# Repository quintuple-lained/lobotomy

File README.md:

# Lobotomy
*The keyboard your therapist told you to worry about.*

An unholy mixture of Alice and Bruce, have fun with this one y'all!

## Images

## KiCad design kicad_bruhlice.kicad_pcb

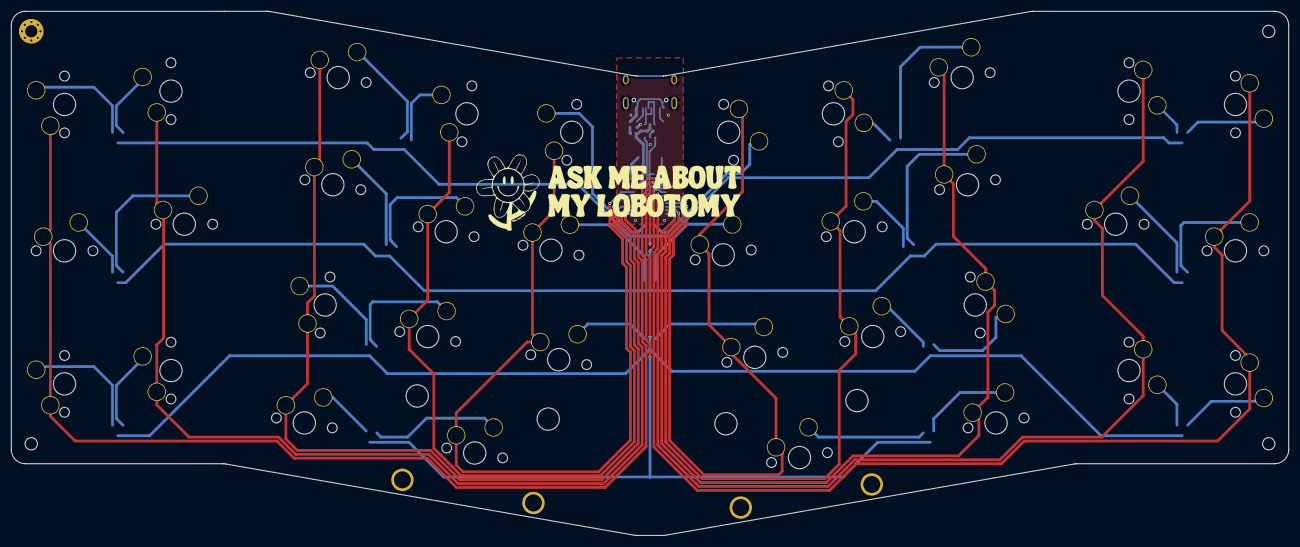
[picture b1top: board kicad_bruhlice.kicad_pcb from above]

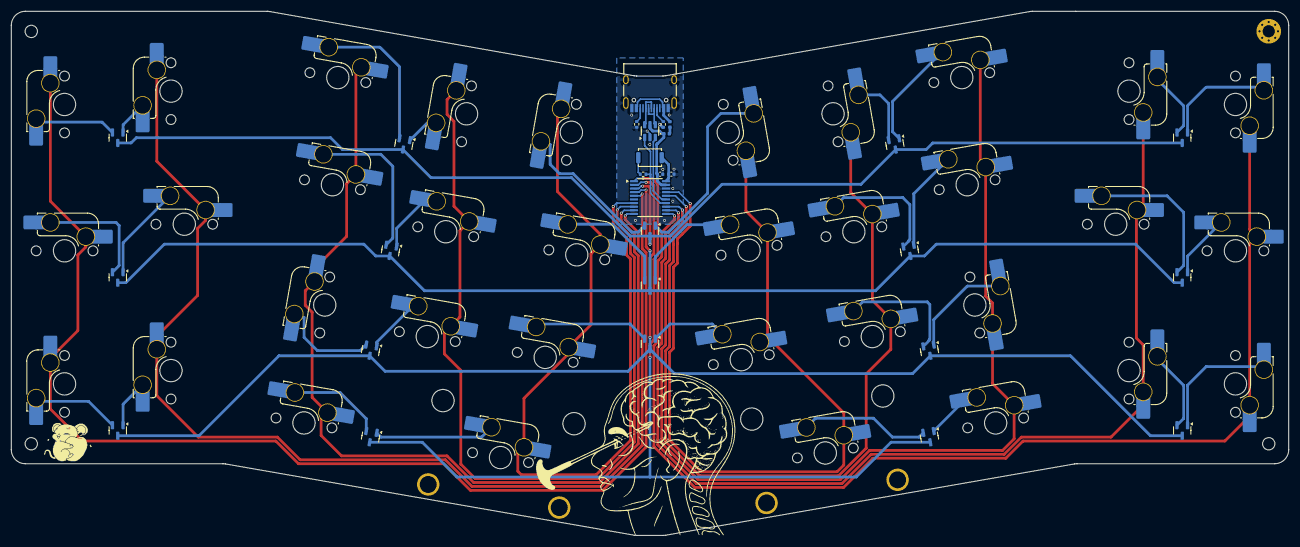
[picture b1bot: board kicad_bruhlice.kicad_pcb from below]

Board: 2 copper layers, 228.6 x 93.8 mm, 68 parts (62 on the bottom side), 60 nets.

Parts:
C1, C2: 100nF; C_0402_1005Metric
D1: PMEG2010EA; D_0402_1005Metric
D2, D3, D4, D5, D6, D7, D8, D9, D10, D11, D12, D13, D14, D15, D16, D17, D18: BAV70_Small; SOT-23
F1: 500mA; Fuse_0402_1005Metric
H1: MountingHole_Pad; MountingHole_2.2mm_M2_Pad_Via_nosilk
H2, H3, H4: MountingHole_Pad; MountingHole_2.2mm_M2
J1: USB_C_Receptacle_USB2.0; USB_C_Receptacle_HRO_TYPE-C-31-M-12
MX1, MX10, MX25, MX31: MX_SW_solder; SW_MX_HS_CPG151101S11_1.75u
MX2, MX3, MX8, MX9, MX16, MX21, MX23, MX26: MX_SW_solder; SW_MX_HS_CPG151101S11_1.5u
MX4, MX5, MX6, MX7, MX12, MX13, MX18, MX19, MX22, MX33, MX34: MX_SW_solder; SW_MX_HS_CPG151101S11_1.25u
MX11, MX14, MX15, MX17, MX20, MX24, MX27, MX28, MX29, MX30, MX32: MX_SW_solder; SW_MX_HS_CPG151101S11_1u
R1, R2: 5.1k; R_0402_1005Metric
R3: 10k; R_0402_1005Metric
S1: MX_stab; STAB_MX_P_2.25u
S2: MX_stab; STAB_MX_P_2.75u
SW1: BOOT; SW_Push_SPST_NO_Alps_SKRK
U1: TSSOP-20_4.4x6.5mm_P0.65mm
U2: USBLC6-2SC6; SOT-23-6

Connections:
+3.3V: C2.1, SW1.2, U1.20 (V33)
BOOT: R3.2, SW1.1
CC1: J1.A5 (CC1), R1.1
CC2: J1.B5 (CC2), R2.1
GND: C1.2, C2.2, H1.1, J1.A1 (GND), J1.A12 (GND), J1.B1 (GND), J1.B12 (GND), J1.S1 (SHIELD), R1.2, R2.2, U1.18 (GND), U2.2 (GND)
unnamed: D1.2 (A), F1.1
unnamed: D2.1 (A1), MX1.2
unnamed: D2.2 (A2), MX2.2
unnamed: D3.1 (A1), MX3.2
unnamed: D3.2 (A2), MX4.2
unnamed: D4.1 (A1), MX5.2
unnamed: D4.2 (A2), MX6.2
unnamed: D5.1 (A1), MX7.2
unnamed: D5.2 (A2), MX8.2
unnamed: D6.1 (A1), MX9.2
unnamed: D6.2 (A2), MX10.2
unnamed: D7.1 (A1), MX11.2
unnamed: D7.2 (A2), MX12.2
unnamed: D8.1 (A1), MX13.2
unnamed: D8.2 (A2), MX14.2
unnamed: D9.1 (A1), MX15.2
unnamed: D9.2 (A2), MX16.2
unnamed: D10.1 (A1), MX17.2
unnamed: D10.2 (A2), MX18.2
unnamed: D11.1 (A1), MX19.2
unnamed: D11.2 (A2), MX20.2
unnamed: D12.1 (A1), MX21.2
unnamed: D12.2 (A2), MX31.2
unnamed: D13.1 (A1), MX22.2
unnamed: D13.2 (A2), MX32.2
unnamed: D14.1 (A1), MX23.2
unnamed: D14.2 (A2), MX33.2
unnamed: D15.1 (A1), MX24.2
unnamed: D15.2 (A2), MX34.2
unnamed: D16.1 (A1), MX25.2
unnamed: D16.2 (A2), MX26.2
unnamed: D17.1 (A1), MX27.2
unnamed: D17.2 (A2), MX28.2
unnamed: D18.1 (A1), MX29.2
unnamed: D18.2 (A2), MX30.2
PORT+: J1.A6 (D+), J1.B6 (D+), U2.6 (I/O1)
PORT-: J1.A7 (D-), J1.B7 (D-), U2.4 (I/O2)
UDM: U1.15 (P3.7), U2.3 (I/O2)
UDP: R3.1, U1.14 (P3.6), U2.1 (I/O1)
VBUS: F1.2, J1.A4 (VBUS), J1.A9 (VBUS), J1.B4 (VBUS), J1.B9 (VBUS)
VCC: C1.1, D1.1 (K), U1.19 (VCC), U2.5 (VBUS)
c0: MX1.1, MX11.1, MX21.1, U1.11 (P3.3)
c1: MX2.1, MX12.1, MX31.1, U1.12 (P3.4)
c2: MX3.1, MX13.1, MX22.1, MX27.1, U1.13 (P3.5)
c3: MX4.1, MX14.1, MX32.1, U1.16 (P1.3)
c4: MX5.1, MX15.1, MX23.1, MX28.1, U1.17 (P1.2)
c5: MX6.1, MX16.1, MX29.1, MX33.1, U1.7 (P1.0)
c6: MX7.1, MX17.1, MX24.1, U1.8 (P1.1)
c7: MX8.1, MX18.1, MX30.1, MX34.1, U1.9 (P3.1)
c8: MX9.1, MX19.1, MX25.1, U1.10 (P3.0)
c9: MX10.1, MX20.1, MX26.1, U1.5 (P1.7)
r0: D2.3 (K), D3.3 (K), D4.3 (K), D5.3 (K), D6.3 (K), U1.3 (P1.5)
r1: D7.3 (K), D8.3 (K), D9.3 (K), D10.3 (K), D11.3 (K), U1.4 (P1.6)
r2: D12.3 (K), D13.3 (K), D14.3 (K), D15.3 (K), D16.3 (K), U1.2 (P1.4)
r3: D17.3 (K), D18.3 (K), U1.1 (P3.2)

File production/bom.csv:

Designator,Footprint,Quantity,Value,LCSC Part #
"C1, C2",0402,2,100nF,C1525
D1,0402,1,PMEG2010EA,C2837790
"D10, D11, D12, D13, D14, D15, D16, D17, D18, D2, D3, D4, D5, D6, D7, D8, D9",SOT-23,17,BAV70_Small,
F1,0402,1,500mA,C210357
H1,MountingHole_2.2mm_M2_Pad_Via_nosilk,1,MountingHole_Pad,
J1,USB_C_Receptacle_HRO_TYPE-C-31-M-12,1,USB_C_Receptacle_USB2.0,C2765186
"MX1, MX10, MX25, MX31",SW_MX_HS_CPG151101S11_1.75u,4,MX_SW_solder,
"MX11, MX14, MX15, MX17, MX20, MX24, MX27, MX28, MX29, MX30, MX32",SW_MX_HS_CPG151101S11_1u,11,MX_SW_solder,
"MX12, MX13, MX18, MX19, MX22, MX33, MX34, MX4, MX5, MX6, MX7",SW_MX_HS_CPG151101S11_1.25u,11,MX_SW_solder,
"MX16, MX2, MX21, MX23, MX26, MX3, MX8, MX9",SW_MX_HS_CPG151101S11_1.5u,8,MX_SW_solder,
"R1, R2",0402,2,5.1k,C25905
R3,0402,1,10k,C25744
S1,STAB_MX_P_2.25u,1,MX_stab,
S2,STAB_MX_P_2.75u,1,MX_stab,
SW1,SW_Push_SPST_NO_Alps_SKRK,1,BOOT,C115357
U1,TSSOP-20_4.4x6.5mm_P0.65mm,1,~,C111367
U2,SOT-23-6,1,USBLC6-2SC6,C2687116

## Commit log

2024-12-16 add switch 3d models and export step
2024-12-16 add stab 3d models
2024-12-17 added render workflow
2024-12-17 fixed?
2024-12-17 fixed a skill issue
2024-12-17 test push please work
